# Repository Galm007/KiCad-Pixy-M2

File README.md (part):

# Pixy-M2 — Micromouse Controller PCB

A controller for a micromouse robot. **On this branch (`devkit-daughterboard`)
the MCU is an ESP32-S3-DevKitC-1-N8R8 plugged into two SMD female headers.**
The board carries two **DRV8231A** motor drivers with current regulation, a
**2S LiPo** power path with fusing, switching and UVLO, a **3.3 V buck**, and
connectors for four **VL53L0X** time-of-flight wall sensors, a **BNO085** IMU
and two **Pololu N20** gearmotors with encoders.

Designed in **KiCad 10**. 4-layer, 66 × 100 mm, fully placed and routed.

| | |
|---|---|
| **MCU** | ESP32-S3-DevKitC-1-**N8R8** (v1.1; 8 MB flash, 8 MB octal PSRAM) on two 1×22 SMD female headers. USB-UART and native-USB ports, BOOT/RESET on the devkit |
| **Power in** | 2S LiPo (7.4 V nominal, 8.4 V full) via XT30. The devkit's USB powers the 3.3 V rail on the bench |
| **Logic rail** | 3.3 V, AP63203 2 A synchronous buck |
| **Motor drive** | 2 × TI DRV8231A H-bridge, 0.828 A nominal hardware current limit, per-motor current sense into the ADC |
| **Sensors** | 4 × VL53L0X ToF (I²C), BNO085 9-DoF IMU (SPI), 2 × 12 CPR quadrature encoders |
| **Protection** | 1500 A-breaking battery fuse, 600 W TVS on the motor rail, hardware UVLO (the devkit carries its own USB protection) |
| **PCB** | 66 × 100 mm, 4 layers, 1.6 mm, 79 footprints, 233 vias, 2.20 m of track |
| **Status** | Schematic complete, ERC 0/0. Layout routed, DRC 0 violations / 0 unconnected / 0 parity. **Not yet fabricated.** |

---

## Contents

- [Board renders](#board-renders)
- [Schematic](#schematic)
- [System architecture](#system-architecture)
- [Design decisions](#design-decisions)
- [Pin and connector reference](#pin-and-connector-reference)
- [PCB layout](#pcb-layout)
- [Parts list](#parts-list)
- [Repository layout](#repository-layout)
- [Working with the project](#working-with-the-project)
- [Bring-up notes for firmware](#bring-up-notes-for-firmware)
- [Status and open items](#status-and-open-items)
- [License](#license)

---

## Board renders

The top of each image is the **front** of the robot: the four ToF sensor
mounts face the maze walls ahead. The devkit stands on its sockets along the
right edge with its antenna over the rear edge. The devkit has no 3D model, so
the renders show Espressif's WROOM-1 model at the module's real height
(11.6 mm) with nothing under it: it floats above the sockets where the
devkit's own PCB would be.

<table>
  <tr>
    <td align="center"><br><b>Top</b></td>
    <td align="center"><br><b>Bottom</b> (mirrored)</td>
  </tr>
</table>

The silkscreen prints where each off-board part attaches:

- **Top:** the four ToF mounts with their aim arrows and the connector each
  cable plugs into, the BNO085 breakout outline (8.6 mm left of the rotation
  centre, beside the devkit), and an arrow between the socket rows toward the
  end that takes the devkit's USB ports.
- **Bottom:** the two Pololu HP 6V gearmotors, with the gearbox face on the
  board edge and the shaft on the wheel axle. `ENC CONN SIDE` marks the face
  their encoder boards stand proud of, which must point outboard. Between the
  motors is the 2S battery's outline, with an arrow at the end its leads
  leave from and a dashed line for the lead's route round the left edge to
  BT1.

---

## Schematic

Single flat A3 sheet: [`Pixy-M2.kicad_sch`](Pixy-M2.kicad_sch).

---

## System architecture

```mermaid
flowchart LR
    BAT["2S LiPo<br/>XT30 (BT1)"] --> F1["F1<br/>5 A fuse<br/>1500 A break"]
    F1 --> Q1["Q1 P-FET<br/>switched by SW3"]
    Q1 -- VBAT --> DRV["U4 / U5<br/>DRV8231A ×2"]
    Q1 -- VBAT --> D6["D6 TVS<br/>SMBJ9.0A"]
    Q1 -- VBAT --> D2["D2<br/>Schottky"]
    D2 -- VSYS --> BUCK["U3 AP63203<br/>3.3 V buck"]
    BUCK -- BUCK_3V3 --> ISO["U8 / Q2<br/>USB-priority isolation"]
    ISO -- ESP_3V3 --> MCU["U1 DevKitC-1<br/>3V3 pins"]
    ISO -- ESP_3V3 --> PERIPH["ToF ×4, IMU,<br/>encoders"]
    USB["devkit USB ports"] --> LDO["devkit LDO"]
    LDO -- 3V3 --> MCU
    DRV --> MOT["J8 / J9<br/>N20 motors + encoders"]
    MCU <-->|I²C| TOF["J4–J7<br/>VL53L0X ×4"]
    MCU <-->|SPI| IMU["J10<br/>BNO085"]
```

### Power path

```
 BT1+ ── F1 ── VBAT_FUSED ── Q1 (S→D) ── VBAT ──┬── D2 ── VSYS ── U3 buck ── BUCK_3V3 ── U8/Q2 ── ESP_3V3 ── devkit 3V3 pins
                   │            │                ├── U4/U5 motor drivers
                  R14           G                ├── R7/R8 UVLO divider
                   └────────────┤                ├── R10/R11 battery sense
                           SW3 (gate only)       └── D6 TVS to GND
```

- **`VBAT`** is the switched, fused motor rail. Motor current does **not** pass
  through D2. D2 feeds only the buck input.
- **`VSYS`** is the pack through D2, **~8.1 V** on a full pack.
- **`BUCK_3V3`** is the buck's regulated output, including L1, C7/C11 and
  its unchanged feedback path. U8 and Q2 feed the separate **`ESP_3V3`** rail.
- **`ESP_3V3`** feeds the devkit's 3V3 pins, sensors, encoders and LEDs.
  U6 supplies the drivers' separate **`MOTOR_VREF`**, nominally 1.242 V.
- **USB has priority.** U1's 5V pin is used only for voltage sensing through
  R28/R29. With USB present, U8 disables and Q2 opens, isolating the buck from
  the devkit LDO. Their opposing body diodes block either direction while off.
  USB therefore supplies the complete logic load; the 800 mA LDO rating alone
  does not establish a safe continuous load. Begin USB bring-up with RF off and
  measure rail voltage and LDO temperature at the intended load.
- **USB removal with the pack on is bridged by C30.** U8 needs ~40 µs to turn
  on once the devkit's LDO drops out; C30 (100 µF X5R) with C1/C15 holds
  ESP_3V3 meanwhile: ≈0.2 V sag at 0.25 A, ≈0.42 V at 0.5 A (conservative,
  without the devkit's own capacitance). Scope it before relying on it.
  USB-only operation leaves the motors inhibited through U6/U7. No on-board
  charging; charge the pack separately.

---

## Design decisions

The rules and rejected alternatives that must not regress are summarised in
[`CLAUDE.md`](CLAUDE.md). The measurements behind each change are under
[`layout/`](layout/), and the full history is in the git log. This section
covers the main choices.

### The MCU as a plug-in DevKitC-1 (this branch)

The ESP32-S3 is an off-the-shelf **ESP32-S3-DevKitC-1-N8R8** on two 1×22
female headers, not a soldered WROOM module. The devkit brings its USB ports,
its USB-UART bridge with auto-reset, its BOOT/RESET buttons and its CHIP_PU RC.
That takes the USB-C input, its ESD array and PPTC, the CC and shield parts,
the USB supply path into VSYS, the reset/boot network and the programming
header off this board, along with the routed USB pair and its impedance
question.

- **Placement.** The devkit is 25.4 × 62.7 mm and fits only along the right
  edge, antenna over the rear edge as before. The board outline is unchanged
  at 66 × 100 mm. The left corner stays the motor and power region; the IMU
  moves into the 25 mm column left beside the devkit, 8.6 mm off the rotation
  centre.
- **SMD sockets.** The devkit's area lies over the underside battery bay and
  motor B; through-hole socket tails would stand into both.
- **Power.** The board's AP63203 feeds the devkit's 3V3 pins, so the verified
  buck block stays. The alternative, a 5 V buck into the devkit's 5V pin,
  would have OR-ed cleanly with USB through the devkit's diodes, but it meant
  redesigning the buck and running everything from an 800 mA LDO.
- **Pins.** The N8R8's octal PSRAM takes GPIO35–37 and the v1.1 board's RGB LED
  takes GPIO38. Encoder B's OUT B moved from GPIO38 to GPIO18, the last spare.
  No GPIO is left spare.
- **Costs.** About 10 mm more height, the devkit's mass, and friction-fit
  headers in a robot that hits walls: retain the devkit before running.

An earlier version put the motors, drivers and IMU on a daughterboard instead,
through two 22-pin headers. That one carried motor return current through the
headers; this one keeps all the power and motor copper on the main board.

### Motor driver: TI DRV8231A

The driver has to survive what the TVS lets through, not just the 8.4 V pack.
D6 clamps `VBAT` at up to **15.4 V**, and that ruled out the usual micromouse
parts:

| Part | VM abs max | Verdict |
|---|---:|---|
| DRV8833 | 11.8 V | below the clamp: rejected |
| TB6612FNG | 15.0 V | below the clamp: rejected |
| DRV8874 / DRV8876 | 40 V | good, but no stock KiCad symbol |
| **DRV8231A** | **35 V** | **fitted**, 2.3× the clamp |

The DRV8231A also:

- runs down to **4.5 V**, which covers the whole usable pack range;
- has **internal 100 kΩ pulldowns on IN1/IN2**, so both motors stay off while
  the ESP32's GPIOs float at reset;
- needs no nSLEEP or nFAULT pin, which saves GPIOs;
- has **integrated current regulation and an `IPROPI` sense output**.

### Current limit: 0.828 A nominal, with connector margin

```
ITRIP = VREF / (AIPROPI × RIPROPI) = 1.242 V / (1500 µA/A × 1 kΩ) = 0.828 A
```

U6's reference replaces the 3.3 V rail at the two driver VREF pins. R17/R18
are **1 kΩ 1 %, ≤100 ppm/°C**. The JST SH contacts and Pololu cable are rated
1 A; the previous 1.00 A nominal setting left no tolerance margin. With the
reference, temperature and resistor corners included, the trip comparator has
about 108 mV margin at 1 A using TI's minimum specified mirror gain. That gain
bound is specified at 1 A and VM ≥6.5 V, so it is not a guarantee on every PWM
peak. Check current ripple and stall heating on hardware.

IPROPI now reads **1.5 V/A** on GPIO2/GPIO10 (ADC1), about 1.242 V at the nominal
limit. Firmware must update its scaling and stop sustained stalls. Details and
calculation assumptions are in [the power integrity audit](layout/power-integrity/README.md).

### Battery fuse: one-time, 1500 A breaking

The chosen pack is a 2S 450 mAh 100C LiPo. Its estimated dead-short current is
**200–400 A**. The original 3 A PPTC could only break 40 A, so it was replaced
with a **Littelfuse 0885005.DR**: 5 A fast-acting, 1500 A breaking at
125 VDC. Normal load is below the old ~2.4 A allowance after lowering both motor
limits. Measure acceleration peaks before changing any fuse or current-limit value. Slow overload protection is now the job of the driver current limit and
firmware stall detection. F1 only opens on a real fault.

### Hardware undervoltage lockout

The buck's `EN` pin has a built-in comparator with switched hysteresis. A 1 %
divider (R7/R8) on `VBAT` sets it to:

| | Pack voltage | Per cell |
|---|---:|---:|
| Turn on | 6.90 V | 3.45 V |
| Turn off | 5.94 V | 2.97 V |

This controls the **buck only**. It cannot stop a USB-powered MCU from driving
motors. The added U6 comparator independently monitors VBAT through R24/R25,
with R26 hysteresis. U7 disconnects all four driver inputs below its threshold;
the drivers' internal pulldowns then command coast regardless of firmware.
U6's power-on reset and R27 keep the switches disabled during logic startup.

| Motor inhibit | Pack voltage | Per cell |
|---|---:|---:|
| Enable on rising battery | 6.75 V | 3.37 V |
| Coast on falling battery | 6.35 V | 3.17 V |

R24/R25/R26 (100 k / 23.2 k / 825 k) are **0.1 %, ≤25 ppm/°C** thin film. Over
−40 to +125 °C the DC envelopes are 6.01–6.74 V (coast) and 6.39–7.08 V
(enable), so a pack resting at 3.6 V/cell always enables the motors. The
inhibit is a hardware **backstop under firmware's own cutoff** (about 6.8 V
under load, latched so a rebounding pack cannot restart a stalled motor).
Below VM 6.5 V the DRV8231A still regulates current; TI just does not
specify its ±6 % mirror accuracy there. (The 2026-10-14 version cut off at
6.92 V and enabled at 7.39 V to stay inside that condition, which cost the
bottom third of the pack.) Filter delay and fast dips need scope checks.
USB does not reach REG_EN.

### Battery sense without a gate FET

`VBAT` → 470 kΩ / 220 kΩ → GPIO1 (ADC1_CH0), with a 100 nF reservoir cap.

- The divider draws 12 µA, well under the 58 µA of the UVLO divider, which
  cannot be gated. A gate FET would save almost nothing.
- A low-side gate would have been harmful: the sense node floats up into the
  GPIO clamp.
- A full-pack reading sits at 2.68 V. Even a badly overcharged 9.5 V pack reads
  3.03 V, still inside the ADC's range.
- Both dividers are downstream of Q1, so SW3 OFF removes their drain on the
  pack.

### Buck converter

- The **AP63203WU** is a fixed 3.3 V part, so it needs no feedback divider.
- **L1 is a Bourns SRP5030T-4R7M** (Isat 6 A, 53 mΩ). It replaced an 0805
  inductor that would have saturated at a few hundred mA.
- **C17 straddles the package under U3**, across IN and GND, which is the
  tightest input loop the pinout allows. C12 (22 µF 25 V 1206) is the bulk. It
  keeps ~11–13 µF at 8.4 V bias, which meets the datasheet's 10 µF effective
  input capacitance.
- **The switch node is 3.57 mm² of top copper with no vias.** TP4 hangs off it
  as a short stub.

### Input diode

D2 is an **onsemi MBRA340T3G** (40 V, 3 A, SMA). It carries only the buck's
input, ~0.43 A worst case, so an ideal-diode controller is not worth it. The
40 V rating covers the 15.4 V TVS clamp reaching `VSYS`. It also blocks the
devkit's USB from back-feeding `VBAT` through the buck.

### IMU on SPI, not I²C

The BNO085 could have shared the ToF I²C bus on throughput alone. It was put
on its own SPI bus for **latency**: an IMU interrupt that arrives mid-way
through a ToF read would wait up to ~150 µs, which is 15 % of a 1 kHz control
period. SCK, MOSI and MISO are on the ESP32-S3's native FSPI pins, so they go
through the IO MUX rather than the GPIO matrix. INT and RST are wired because
the BNO08x needs both for stable SPI. WAKE shares a pin with PS0 on the module.

### Four ToF sensors on one I²C bus

Every VL53L0X powers up at address `0x29`, and the address is volatile. Each
sensor therefore gets its own XSHUT line (GPIO4–7), so firmware can release the
sensors one at a time and re-address them. R15/R16 (2.2 kΩ) are the only bus
pull-ups, placed near the host, as the datasheet recommends. J4–J7 use the
GY-VL53L0XV2 module's own header order, so the cable is a straight 1:1 loom.

### USB

On the devkit. Its native-USB port (USB-Serial-JTAG) gives flashing, console
and debugging; its USB-UART port gives esptool auto-reset. Each port reaches
the devkit's 5 V rail through a 1N5819. This board senses that rail at U1.21
for USB priority; it does not draw supply power from it.

### Strapping pins

GPIO45 and GPIO46 carry explicit no-connect flags. Driving GPIO45 high at reset
sets the flash rail to 1.8 V and the board will not boot. GPIO46 high with
GPIO0 low is an invalid boot combination. GPIO0 is the devkit's BOOT button.
GPIO3 is the safe one of the four, and drives the green status LED
active-high, so its reset state stays low.

### Capacitor ratings

Every capacitor's voltage rating is in its Value field, so it shows on the
schematic. One is worth pointing out:

- **C19/C21** (motor bulk) are **22 µF 25 V** because of the 15.4 V TVS clamp.

---

## Pin and connector reference

### GPIO allocation

Every GPIO the devkit leaves usable is allocated; none is spare.

| Function | GPIO |
|---|---|
| Devkit USB D− / D+ (not wired here) | 19 / 20 |
| Devkit BOOT button (not wired here) | 0 |
| Battery sense (ADC1_CH0) | 1 |
| Status LED (green, active high) | 3 |
| ToF XSHUT 1–4 (J4–J7) | 4, 5, 6, 7 |
| I²C SDA / SCL (ToF bus) | 8 / 9 |
| Motor A IN1 / IN2 | 39 / 40 |
| Motor B IN1 / IN2 | 41 / 42 |
| Motor A / B current sense (IPROPI, ADC1) | 2 / 10 |
| Encoder A: OUT A / OUT B | 47 / 48 |
| Encoder B: OUT A / OUT B | 21 / 18 |
| IMU SPI SCK / MOSI / MISO / CS | 12 / 11 / 13 / 14 |
| IMU INT / RST / WAKE (PS0) | 15 / 16 / 17 |
| Devkit USB-UART TX / RX (not wired here) | 43 / 44 |
| N8R8 octal PSRAM / v1.1 RGB LED (not wired here) | 35, 36, 37 / 38 |
| Strapping, deliberately no-connect | 45, 46 |

### Connectors

All the signal connectors are **JST SH 1.0 mm side-entry**.

**J4–J7: VL53L0X ToF sensors** (`SM06B-SRSS-TB`, GY-VL53L0XV2 header order)

| Pin | 1 | 2 | 3 | 4 | 5 | 6 |
|---|---|---|---|---|---|---|
| Signal | **VCC 3.3 V** | GND | SCL | SDA | INT (NC) | XSHUT |

> ⚠️ Pin 1 is **VCC**, not GND. A cable built "the usual way round" puts
> 3.3 V on the sensor's ground.

| Connector | Position | XSHUT |
|---|---|---|
| J4 | Front left (FL) | GPIO4 |
| J5 | Front right (FR) | GPIO5 |
| J6 | Look-ahead left, 45° | GPIO6 |
| J7 | Look-ahead right, 45° | GPIO7 |

**J8 / J9: motor + encoder** (`SM06B-SRSS-TB`, Pololu 12 CPR encoder order)

| Pin | 1 | 2 | 3 | 4 | 5 | 6 | MP |
|---|---|---|---|---|---|---|---|
| Signal | GND | OUT B | OUT A | VCC 3.3 V | M2 | M1 | GND |
| Pololu wire | green | white | yellow | blue | black | red | — |

J8 is motor A (left) and J9 is motor B (right). Use Pololu's straight SH–SH
encoder cable (#4765–#4769). R19–R22 pull the encoder outputs up to 3.3 V.

**J10: BNO085 IMU** (`SM09B-SRSS-TB`)

| Pin | 1 | 2 | 3 | 4 | 5 | 6 | 7 | 8 | 9 |
|---|---|---|---|---|---|---|---|---|---|
| Signal | VIN 3.3 V | GND | SCK | MOSI | MISO | CS | INT | RST | WAKE / PS0 |

> ⚠️ Jumper **PS1 high** on the module. Stock BNO08x breakouts ship in I²C mode
> and will not answer on SPI until it is changed.

**U1: the DevKitC-1** (two 1×22 2.54 mm SMD female headers)

The devkit plugs in with its **USB ports toward the front** of the robot: the
silkscreen arrow between the rows points that way, and `3V3`/`GND` mark pins
1/44 at the antenna end. Turned round, it puts the 3.3 V rail on GND pins.
Its USB-UART port is the way back in if firmware ever disables the native USB.

**Other**

| Ref | Part | Purpose |
|---|---|---|
| BT1 | XT30U-M | 2S LiPo input |
| SW3 | C&K JS102011SAQN slide | Battery ON/OFF (gate control only) |
| D4 / D5 | Red / green LED | Power (always on) / status (GPIO3), rear-left corner |
| TP1–TP4 | Test pads | VBAT, 3V3, GND, SW node (TP4 is under the devkit's USB end; TP2/TP3 sit between J5 and J7) |
| TP9 | Test pad | Probe GND |
| TP10, TP11 | Test pads | MOTOR_OK (rear left), MOTOR_VREF (beside the motor corner). BUCK_3V3 is probed at L1 or C26, in front of the devkit |

---

## PCB layout

### Stackup

4 layers, 1.6 mm, designed for **JLC04161H-7628** (~0.2 mm L1–L2 prepreg).

| Layer | Use |
|---|---|
| **L1** F.Cu | Components, buck switch node, motor-driver power loops, ground pour around the motor region |
| **L2** In1.Cu | **Solid, unbroken GND plane.** No signals, no splits. |
| **L3** In2.Cu | `ESP_3V3` pour plus a separate `VBAT` island under the motor region |
| **L4** B.Cu | Secondary routing plus a GND pour stitched to L2 |

The ground plane is never split. Noise is controlled by **placement**
instead. The motor drivers, the bulk capacitors, D6 and the battery entry
share the left-hand region. The devkit, ADC nodes and I²C sit away from it.

<p align="center">
  <br>
  <em>Top copper (F.Cu). The 0.8 mm motor trunks, the 1.0 mm battery path and the motor-region ground pour are on the left.</em>
</p>

### Layout highlights

- **Every trace is straight 0/45/90° runs with 45° turns.** The grid router's
  staircases, which rendered as curves, are rebuilt as clear straight legs by
  the last copper stage ([`layout/octilinear/`](layout/octilinear/README.md)).
  Only hand-placed copper keeps its own geometry: the buck block, the driver
  pin escapes and their bypass loops, ten short stubs in all off 45°.
- **Motor outputs** are 0.8 mm trunks. The only narrower copper is inside
  each driver's own pin field, and a custom DRC rule enforces that. Each pair
  runs together to its connector: the loop areas are **25.9 mm²** (A) and
  **24.3 mm²** (B).
- **Driver thermal pads** each have two filled-and-capped in-pad vias
  (IPC-4761 type VII) plus four more nearby. Only two fit a 0.9 × 1.6 mm pad
  under the hole-to-hole rule.
- **VM bypass caps** sit 1.33 mm from each driver's VM pin, across VM and GND.
  The loop closes in top copper with no plane hop.
- **Antenna keep-out**: the devkit's antenna overhangs the rear edge ~10 mm
  above the board, with an all-layer copper keep-out under its edge defined as
  a board rule area.
- **The devkit stands on SMD sockets.** Its courtyard is the two socket
  bodies; low parts (C1/C2, the I²C and encoder pull-ups) sit between the rows
  under it.
- **Rules are encoded, not just followed.** Netclasses and
  [`Pixy-M2.kicad_dru`](Pixy-M2.kicad_dru) enforce:
  - motor trunk width;
  - power and battery path widths;
  - a 0.2 mm signal floor;
  - clearance floors keeping `REG_EN`, `VBAT_SENSE` and the IPROPI lines away
    from motor and switching copper.

  Each rule was tested by breaking a copy of the board and checking that DRC
  fired.

The board was routed by a purpose-written A* grid router
([`tools/autoroute/`](tools/autoroute/)) and then reworked in stages, each
driven by a design review. Every stage is scripted and reproducible. The review
findings and the evidence for each fix (DRC reports, measurements,
before/after images) are under [`layout/`](layout/).

---

## Parts list

Parts for **one robot**, taken from **[`BOM.md`](BOM.md)**. BOM.md also has
each part's status, the cable wiring, the mechanical parts and the tools. The
shopping list below has one line per part to buy.

### Shopping list

Quantities are exact, with no spares except the crimp contacts. Where BOM.md
lets one part fill several positions, the list merges them: one 0.1 µF 50 V
part covers all twelve 0.1 µF positions. R24–R26 must be 0.1 % and ≤25 ppm/°C; other
resistors may be 1 %. R17/R18 and R28/R29 must also be ≤100 ppm/°C.

| Qty | Part | For |
|---:|---|---|
| 1 | Espressif **ESP32-S3-DevKitC-1-N8R8** (v1.1) | U1, plugged in. Not an `R8V`/`R16V` variant (1.8 V GPIO47/48) |
| 2 | 1×22 2.54 mm vertical **SMD** female header, Harwin M20-786 land pattern | U1's sockets. Part number open: see BOM.md |
| 2 | TI **DRV8231ADSGR** | U4, U5 |
| 1 | Diodes Inc **AP63203WU-7** | U3. Fixed 3.3 V, not the AP63200 |
| 1 | TI **TLV3012BIDBVR** | U6; B version required |
| 1 | TI **SN74LV4066APWR** | U7 |
| 1 | TI **LM66100DCKR** | U8 |
| 1 | AOS **AO3401A** | Q2 |
| 1 | onsemi **MMBT3904LT1G** | Q3 |
| 1 | AOS **AO4407A** | Q1. Not the IRF7404 the symbol names |
| 1 | onsemi **MBRA340T3G** | D2 |
| 1 | Vishay **SMBJ9.0A-E3/52** | D6 |
| 1 | Red LED, high-efficiency, 0805 | D4. Must be visibly lit at ~150 µA |
| 1 | Green LED, 0805 | D5 |
| 1 | Bourns **SRP5030T-4R7M** | L1 |
| 1 | Littelfuse **0885005.DR** | F1 |
| 1 | C&K **JS102011SAQN** | SW3 |
| 1 | AMASS **XT30U-M** | BT1 |
| 6 | JST **SM06B-SRSS-TB(LF)(SN)** | J4–J9 |
| 1 | JST **SM09B-SRSS-TB(LF)(SN)** | J10 |
| 12 | 0.1 µF 50 V X7R, 0603 | C2, C6, C13, C14, C16–C18, C20, C22–C24, C27 |
| 1 | 2.2 nF 16 V X7R, 0603 | C25 |
| 1 | 4.7 nF 16 V X7R, 0603 | C28 |
| 1 | 1 µF 16 V X7R, 0603 | C26 |
| 1 | Murata **GRM31CR60J107ME39L**, 100 µF 6.3 V X5R, 1206 | C30 |
| 2 | 10 µF 16 V X5R/X7R, 0805 | C1, C15 |
| 2 | 22 µF 16 V X5R/X7R, 0805 | C7, C11 |
| 3 | 22 µF 25 V X5R/X7R, 1206 | C12, C19, C21 |
| 7 | 10 kΩ 1 %, 0805 | R12, R19–R23, R28 |
| 3 | 2.2 kΩ 1 %, 0805 | R13, R15, R16 |
| 2 | 1 kΩ 1 %, ≤100 ppm/°C, 0805 | R17/R18, RC0805FR-071KL |
| 1 | 82 kΩ 1 %, 0805 | R29 |
| 1 | Yageo **RT0805BRD07100KL**, 100 kΩ 0.1 % 25 ppm, 0805 | R24 |
| 1 | Yageo **RT0805BRD0723K2L**, 23.2 kΩ 0.1 % 25 ppm, 0805 | R25 |
| 1 | Yageo **RT0805BRD07825KL**, 825 kΩ 0.1 % 25 ppm, 0805 | R26 |
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
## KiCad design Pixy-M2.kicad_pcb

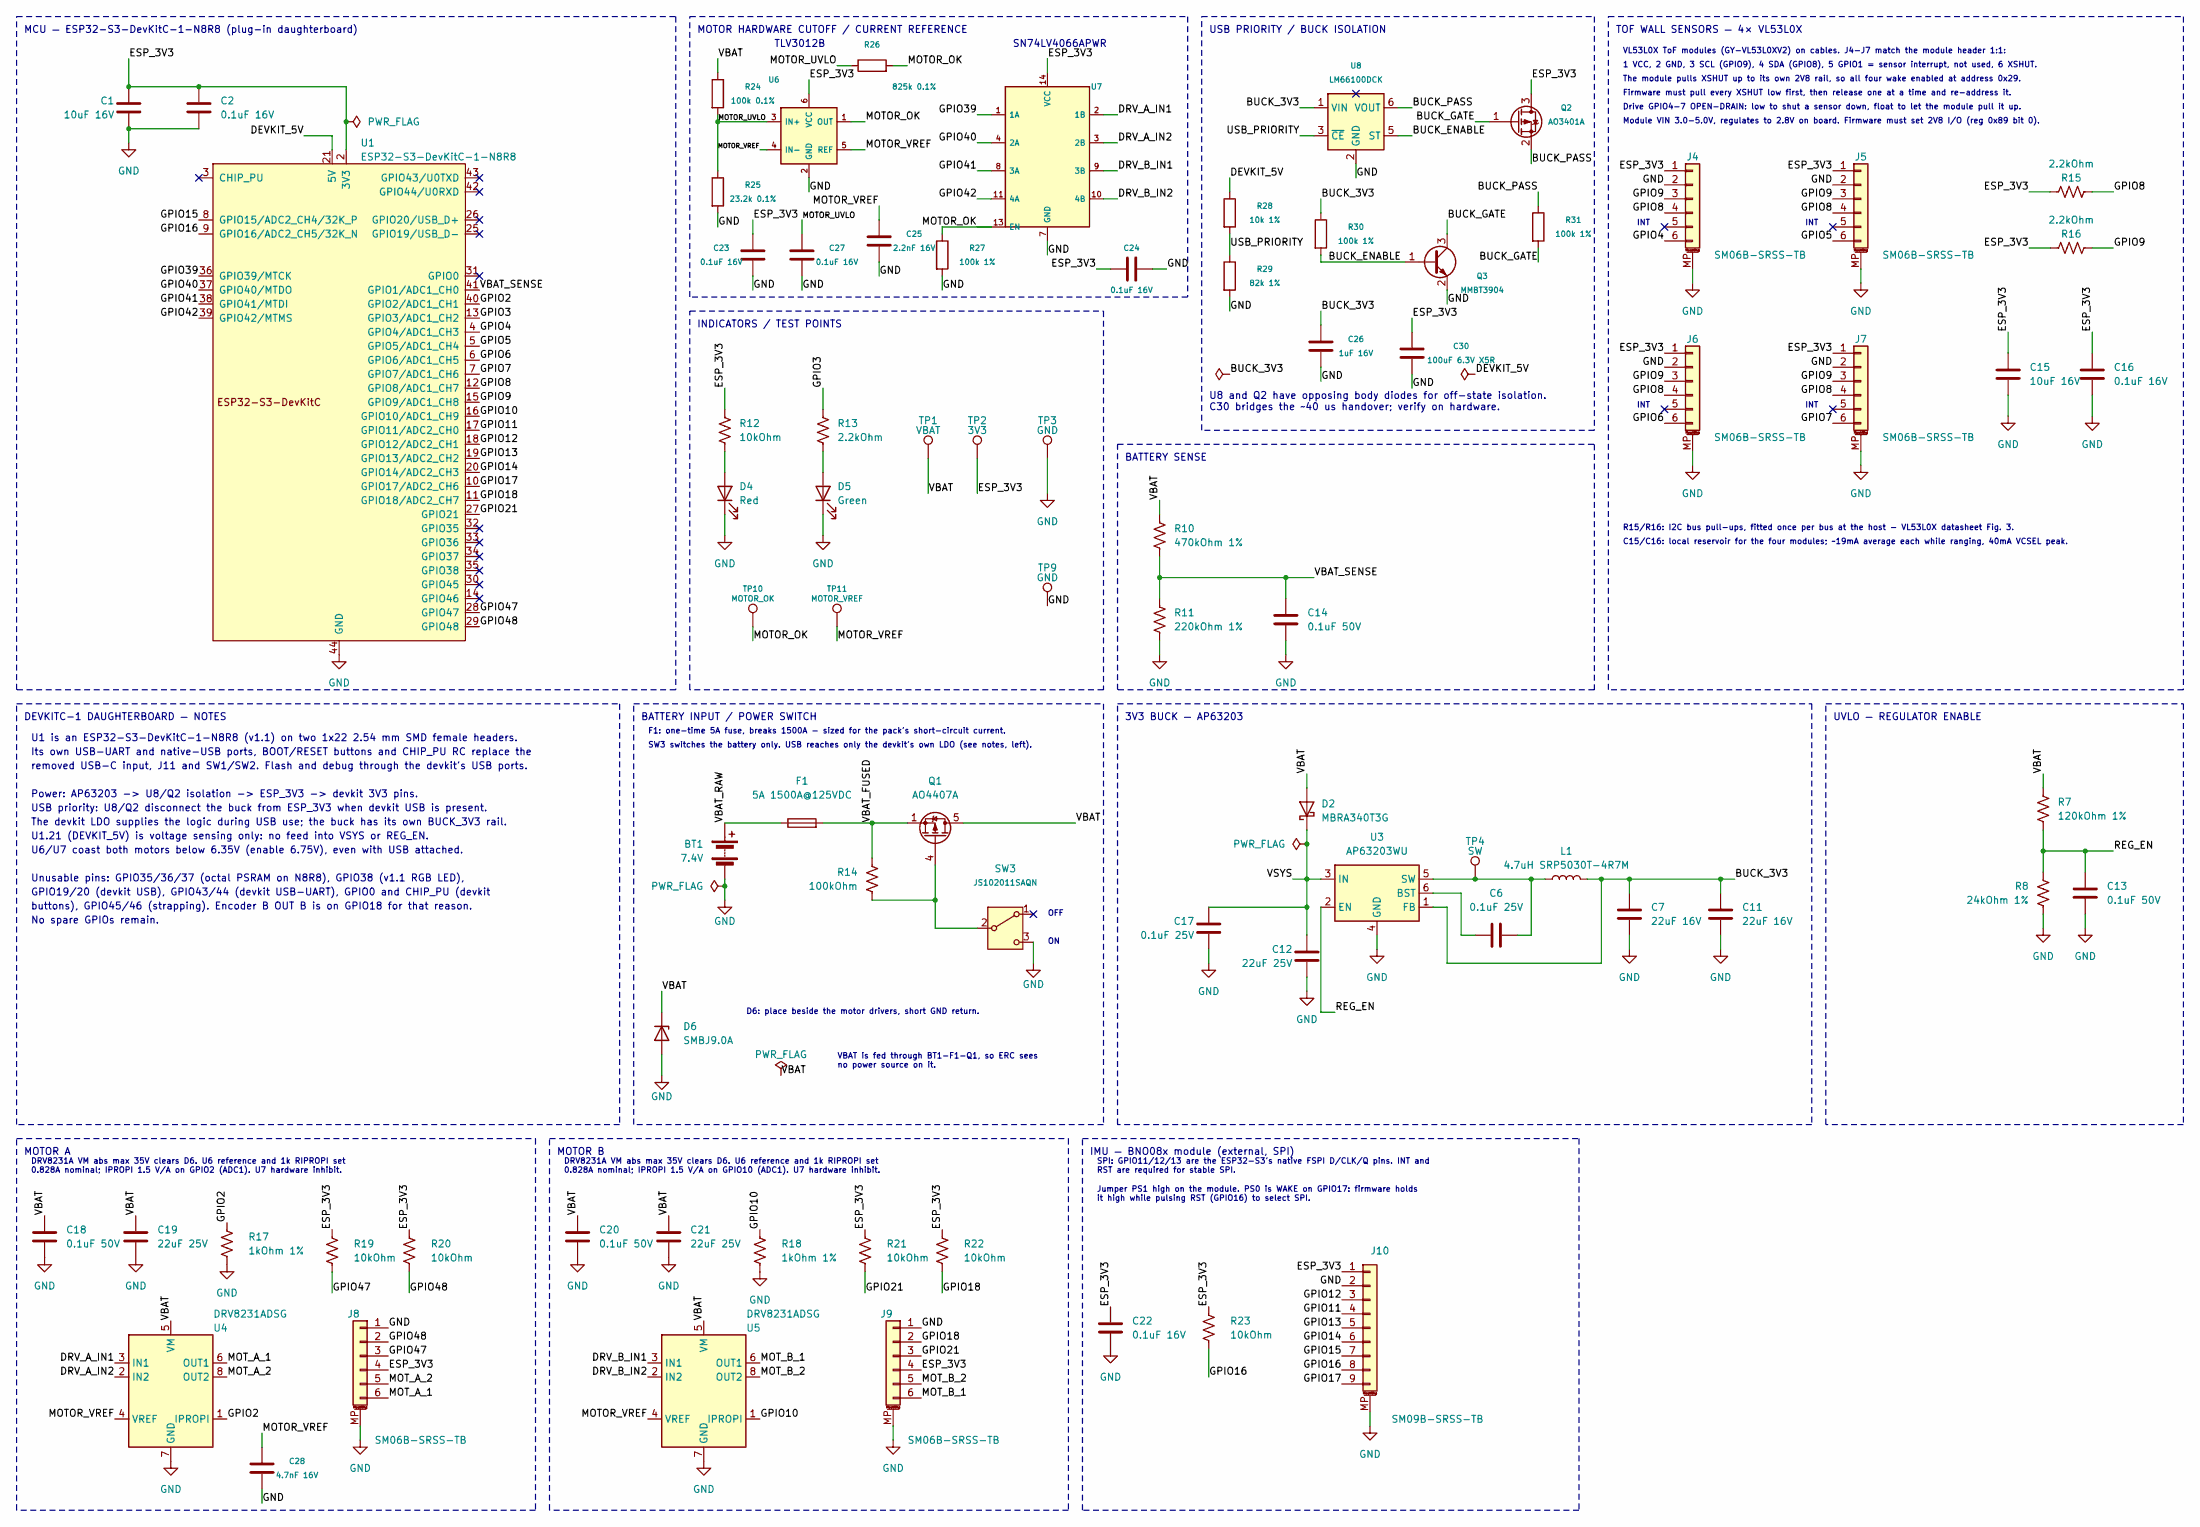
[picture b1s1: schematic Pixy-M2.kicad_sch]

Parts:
BT1: 7.4V; AMASS_XT30U-M_1x02_P5.0mm_Vertical
C1, C15: 10uF 16V; C_0805_2012Metric
C2, C16, C22, C23, C24, C27: 0.1uF 16V; C_0603_1608Metric
C6, C17: 0.1uF 25V; C_0603_1608Metric
C7, C11: 22uF 16V; C_0805_2012Metric
C12, C19, C21: 22uF 25V; C_1206_3216Metric
C13, C14, C18, C20: 0.1uF 50V; C_0603_1608Metric
C25: 2.2nF 16V; C_0603_1608Metric
C26: 1uF 16V; C_0603_1608Metric
C28: 4.7nF 16V; C_0603_1608Metric
C30: 100uF 6.3V X5R; C_1206_3216Metric; MPN GRM31CR60J107ME39L
D2: MBRA340T3G; D_SMA; MPN MBRA340T3G
D4: Red; LED_0805_2012Metric
D5: Green; LED_0805_2012Metric
D6: SMBJ9.0A; D_SMB; MPN SMBJ9.0A-E3/52
F1: 5A 1500A@125VDC; Fuse_Littelfuse-NANO2-885; MPN 0885005.DR
J4, J5, J6, J7, J8, J9: SM06B-SRSS-TB; JST_SH_SM06B-SRSS-TB_1x06-1MP_P1.00mm_Horizontal; MPN SM06B-SRSS-TB(LF)(SN)
J10: SM09B-SRSS-TB; JST_SH_SM09B-SRSS-TB_1x09-1MP_P1.00mm_Horizontal
L1: 4.7uH SRP5030T-4R7M; L_Bourns_SRP5030T; MPN SRP5030T-4R7M
Q1: AO4407A; SOIC-8_3.9x4.9mm_P1.27mm; MPN AO4407A
Q2: AO3401A; SOT-23; MPN AO3401A
Q3: MMBT3904; SOT-23; MPN MMBT3904LT1G
R7: 120kOhm 1%; R_0805_2012Metric
R8: 24kOhm 1%; R_0805_2012Metric
R10: 470kOhm 1%; R_0805_2012Metric
R11: 220kOhm 1%; R_0805_2012Metric
R12, R19, R20, R21, R22, R23: 10kOhm; R_0805_2012Metric
R13, R15, R16: 2.2kOhm; R_0805_2012Metric
R14: 100kOhm; R_0805_2012Metric
R17, R18: 1kOhm 1%; R_0805_2012Metric; MPN RC0805FR-071KL
R24: 100k 0.1%; R_0805_2012Metric; MPN RT0805BRD07100KL
R25: 23.2k 0.1%; R_0805_2012Metric; MPN RT0805BRD0723K2L
R26: 825k 0.1%; R_0805_2012Metric; MPN RT0805BRD07825KL
R27, R30, R31: 100k 1%; R_0805_2012Metric
R28: 10k 1%; R_0805_2012Metric
R29: 82k 1%; R_0805_2012Metric
SW3: JS102011SAQN; SW_SPDT_CK_JS102011SAQN; MPN JS102011SAQN
TP1: VBAT; TestPoint_Pad_D1.5mm
TP2: 3V3; TestPoint_Pad_D1.5mm
TP3, TP9: GND; TestPoint_Pad_D1.5mm
TP4: SW; TestPoint_Pad_D1.5mm
TP10: MOTOR_OK; TestPoint_Pad_D1.5mm
TP11: MOTOR_VREF; TestPoint_Pad_D1.5mm
U1: ESP32-S3-DevKitC-1-N8R8; ESP32-S3-DevKitC-1_SMD_Sockets; MPN ESP32-S3-DevKitC-1-N8R8
U3: AP63203WU; TSOT-23-6
U4, U5: DRV8231ADSG; Texas_DSG0008A_WSON-8-1EP_2x2mm_P0.5mm_EP0.9x1.6mm; MPN DRV8231ADSGR
U6: TLV3012B; SOT-23-6; MPN TLV3012BIDBVR
U7: SN74LV4066APW; TSSOP-14_4.4x5mm_P0.65mm; MPN SN74LV4066APWR
U8: LM66100DCK; SOT-363_SC-70-6; MPN LM66100DCKR

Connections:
/BUCK_3V3: C7.1, C11.1, C26.1, L1.2, R30.1, U3.1 (FB), U8.1 (VIN)
/BUCK_ENABLE: Q3.1 (B), R30.2, U8.5 (ST)
/BUCK_GATE: Q2.1 (G), Q3.3 (C), R31.2
/BUCK_PASS: Q2.2 (S), R31.1, U8.6 (VOUT)
/DEVKIT_5V: R28.1, U1.21 (5V)
/DRV_A_IN1: U4.3 (IN1), U7.2 (1B)
/DRV_A_IN2: U4.2 (IN2), U7.3 (2B)
/DRV_B_IN1: U5.3 (IN1), U7.9 (3B)
/DRV_B_IN2: U5.2 (IN2), U7.10 (4B)
/ESP_3V3: C1.1, C2.1, C15.1, C16.1, C22.1, C23.1, C24.1, C30.1, J4.1, J5.1, J6.1, J7.1, J8.4, J9.4, J10.1, Q2.3 (D), R12.1, R15.1, R16.1, R19.1, R20.1, R21.1, R22.1, R23.1, TP2.1, U1.1 (3V3), U1.2 (3V3), U6.6 (VCC), U7.14 (VCC)
/GPIO2: R17.1, U1.40 (GPIO2/ADC1_CH1), U4.1 (IPROPI)
/GPIO3: R13.1, U1.13 (GPIO3/ADC1_CH2)
/GPIO4: J4.6, U1.4 (GPIO4/ADC1_CH3)
/GPIO5: J5.6, U1.5 (GPIO5/ADC1_CH4)
/GPIO6: J6.6, U1.6 (GPIO6/ADC1_CH5)
/GPIO7: J7.6, U1.7 (GPIO7/ADC1_CH6)
/GPIO8: J4.4, J5.4, J6.4, J7.4, R15.2, U1.12 (GPIO8/ADC1_CH7)
/GPIO9: J4.3, J5.3, J6.3, J7.3, R16.2, U1.15 (GPIO9/ADC1_CH8)
/GPIO10: R18.1, U1.16 (GPIO10/ADC1_CH9), U5.1 (IPROPI)
/GPIO11: J10.4, U1.17 (GPIO11/ADC2_CH0)
/GPIO12: J10.3, U1.18 (GPIO12/ADC2_CH1)
/GPIO13: J10.5, U1.19 (GPIO13/ADC2_CH2)
/GPIO14: J10.6, U1.20 (GPIO14/ADC2_CH3)
/GPIO15: J10.7, U1.8 (GPIO15/ADC2_CH4/32K_P)
/GPIO16: J10.8, R23.2, U1.9 (GPIO16/ADC2_CH5/32K_N)
/GPIO17: J10.9, U1.10 (GPIO17/ADC2_CH6)
/GPIO18: J9.2, R22.2, U1.11 (GPIO18/ADC2_CH7)
/GPIO21: J9.3, R21.2, U1.27 (GPIO21)
/GPIO39: U1.36 (GPIO39/MTCK), U7.1 (1A)
/GPIO40: U1.37 (GPIO40/MTDO), U7.4 (2A)
/GPIO41: U1.38 (GPIO41/MTDI), U7.8 (3A)
/GPIO42: U1.39 (GPIO42/MTMS), U7.11 (4A)
/GPIO47: J8.3, R19.2, U1.28 (GPIO47)
/GPIO48: J8.2, R20.2, U1.29 (GPIO48)
/MOTOR_OK: R26.2, R27.1, TP10.1, U6.1 (OUT), U7.5, U7.6, U7.12, U7.13 (EN)
/MOTOR_UVLO: C27.1, R24.2, R25.1, R26.1, U6.3 (IN+)
/MOTOR_VREF: C25.1, C28.1, TP11.1, U4.4 (VREF), U5.4 (VREF), U6.4 (IN-), U6.5 (REF)
/MOT_A_1: J8.6, U4.6 (OUT1)
/MOT_A_2: J8.5, U4.8 (OUT2)
/MOT_B_1: J9.6, U5.6 (OUT1)
/MOT_B_2: J9.5, U5.8 (OUT2)
/REG_EN: C13.1, R7.2, R8.1, U3.2 (EN)
/USB_PRIORITY: R28.2, R29.1, U8.3 (~CE)
/VBAT: C18.1, C19.1, C20.1, C21.1, D2.2 (A), D6.1 (K), Q1.5 (D), Q1.6 (D), Q1.7 (D), Q1.8 (D), R7.1, R10.1, R24.1, TP1.1, U4.5 (VM), U5.5 (VM)
/VBAT_FUSED: F1.2, Q1.1 (S), Q1.2 (S), Q1.3 (S), R14.1
/VBAT_RAW: BT1.1 (+), F1.1
/VBAT_SENSE: C14.1, R10.2, R11.1, U1.41 (GPIO1/ADC1_CH0)
/VSYS: C12.1, C17.1, D2.1 (K), U3.3 (IN)
GND: BT1.2 (-), C1.2, C2.2, C7.2, C11.2, C12.2, C13.2, C14.2, C15.2, C16.2, C17.2, C18.2, C19.2, C20.2, C21.2, C22.2, C23.2, C24.2, C25.2, C26.2, C27.2, C28.2, C30.2, D4.1 (K), D5.1 (K), D6.2 (A), J4.2, J4.MP (MountPin), J5.2, J5.MP (MountPin), J6.2, J6.MP (MountPin), J7.2, J7.MP (MountPin), J8.1, J8.MP (MountPin), J9.1, J9.MP (MountPin), J10.2, J10.MP (MountPin), Q3.2 (E), R8.2, R11.2, R17.2, R18.2, R25.2, R27.2, R29.2, SW3.3 (C), TP3.1, TP9.1, U1.22 (GND), U1.23 (GND), U1.24 (GND), U1.44 (GND), U3.4 (GND), U4.7 (GND), U4.9 (GND), U5.7 (GND), U5.9 (GND), U6.2 (GND), U7.7 (GND), U8.2 (GND)
unnamed: D4.2 (A), R12.2
unnamed: D5.2 (A), R13.2
unnamed: Q1.4 (G), R14.2, SW3.2 (B)
unnamed: C6.1, U3.6 (BST)
unnamed: C6.2, L1.1, TP4.1, U3.5 (SW)

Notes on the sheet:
OFF
F1: one-time 5A fuse, breaks 1500A - sized for the pack's short-circuit current.
SW3 switches the battery only. USB reaches only the devkit's own LDO (see notes, left).
D6: place beside the motor drivers, short GND return.
INT
VL53L0X ToF modules (GY-VL53L0XV2) on cables. J4-J7 match the module header 1:1:
1 VCC, 2 GND, 3 SCL (GPIO9), 4 SDA (GPIO8), 5 GPIO1 = sensor interrupt, not used, 6 XSHUT.
The module pulls XSHUT up to its own 2V8 rail, so all four wake enabled at address 0x29.
Firmware must pull every XSHUT low first, then release one at a time and re-address it.
Drive GPIO4-7 OPEN-DRAIN: low to shut a sensor down, float to let the module pull it up.
Module VIN 3.0-5.0V, regulates to 2.8V on board. Firmware must set 2V8 I/O (reg 0x89 bit 0).
R15/R16: I2C bus pull-ups, fitted once per bus at the host - VL53L0X datasheet Fig. 3.
C15/C16: local reservoir for the four modules; ~19mA average each while ranging, 40mA VCSEL peak.
MOTOR A
DRV8231A VM abs max 35V clears D6. U6 reference and 1k RIPROPI set 0.828A nominal; IPROPI 1.5 V/A on GPIO2 (ADC1). U7 hardware inhibit.
MOTOR B
DRV8231A VM abs max 35V clears D6. U6 reference and 1k RIPROPI set 0.828A nominal; IPROPI 1.5 V/A on GPIO10 (ADC1). U7 hardware inhibit.
VBAT is fed through BT1-F1-Q1, so ERC sees no power source on it.
IMU — BNO08x module (external, SPI)
SPI: GPIO11/12/13 are the ESP32-S3's native FSPI D/CLK/Q pins. INT and RST are required for stable SPI.
Jumper PS1 high on the module. PS0 is WAKE on GPIO17: firmware holds it high while pulsing RST (GPIO16) to select SPI.
MCU — ESP32-S3-DevKitC-1-N8R8 (plug-in daughterboard)
INDICATORS / TEST POINTS
BATTERY SENSE
TOF WALL SENSORS — 4× VL53L0X
DEVKITC-1 DAUGHTERBOARD — NOTES
BATTERY INPUT / POWER SWITCH
3V3 BUCK — AP63203
UVLO — REGULATOR ENABLE
U1 is an ESP32-S3-DevKitC-1-N8R8 (v1.1) on two 1x22 2.54 mm SMD female headers.
Its own USB-UART and native-USB ports, BOOT/RESET buttons and CHIP_PU RC replace the
removed USB-C input, J11 and SW1/SW2. Flash and debug through the devkit's USB ports.
Power: AP63203 -> U8/Q2 isolation -> ESP_3V3 -> devkit 3V3 pins.
USB priority: U8/Q2 disconnect the buck from ESP_3V3 when devkit USB is present.
The devkit LDO supplies the logic during USB use; the buck has its own BUCK_3V3 rail.
U1.21 (DEVKIT_5V) is voltage sensing only: no feed into VSYS or REG_EN.
U6/U7 coast both motors below 6.35V (enable 6.75V), even with USB attached.
Unusable pins: GPIO35/36/37 (octal PSRAM on N8R8), GPIO38 (v1.1 RGB LED),
GPIO19/20 (devkit USB), GPIO43/44 (devkit USB-UART), GPIO0 and CHIP_PU (devkit
buttons), GPIO45/46 (strapping). Encoder B OUT B is on GPIO18 for that reason.

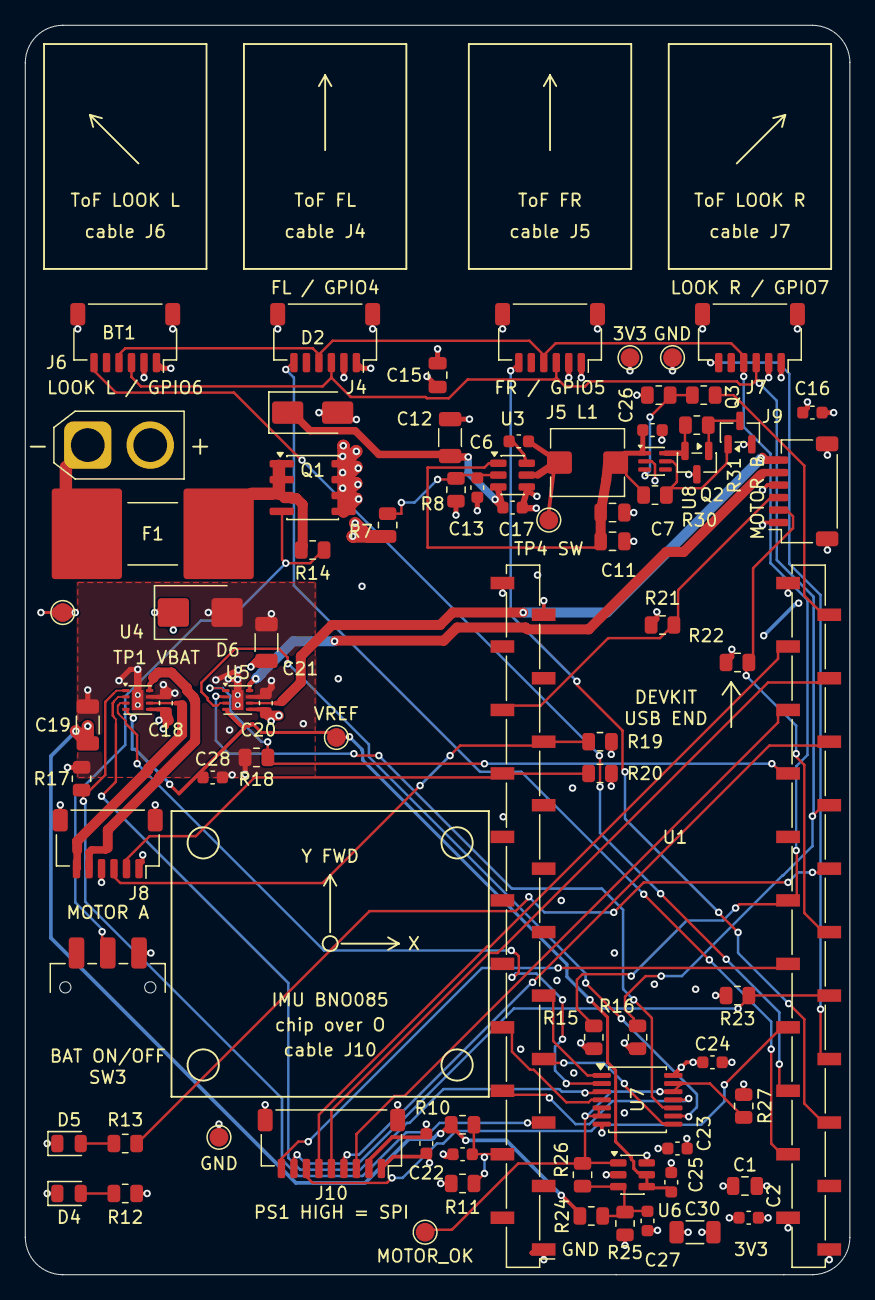
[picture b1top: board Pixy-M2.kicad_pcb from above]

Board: 4 copper layers, 66.0 x 100.0 mm, 79 parts (0 on the bottom side), 54 nets.

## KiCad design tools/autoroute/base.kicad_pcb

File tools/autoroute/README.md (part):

# autoroute — the grid router used to wire Pixy-M2 on 2026-09-21

Not a general tool. It was written for this board and hard-codes its net names,
widths and the In2.Cu VBAT island.

    python3 wire.py      # reads base.kicad_pcb, writes ../../Pixy-M2.kicad_pcb
    python3 rework.py    # reads base-routed.kicad_pcb, writes ../../Pixy-M2.kicad_pcb
    python3 check.py     # per-net length / width / via report on the routed board
    python3 loop.py -v   # motor output pair loop areas (add paths to compare boards)

A full `rework.py` run takes a few minutes: the via-out-of-pad pass recomputes a
per-net distance field for each via it moves. Run it in the background rather than
waiting on it, and **do not watch it with `pgrep -f "python3 rework.py"`** — the
pattern matches the watching shell's own command line, so the loop never exits.

## wire.py — the original routing pass

`wire.py` expects an *unrouted* copy of the board as `base.kicad_pcb` in its working
directory, and rewrites the project file from scratch every run — it never edits
existing tracks. Re-running it discards all hand edits made since, so copy the board
aside first.

How it works: pads and holes are rasterised onto a 0.05 mm grid; per net a Euclidean
distance transform gives the legal region for that net's width (0.26 mm clearance
target against a 0.2 mm rule); A* over F.Cu + B.Cu with a via cost routes each net,
growing a connected group at a time. Plane nets get one stitching via per SMD pad
instead of being routed. A final pass widens power tracks wherever clearance allows.

Two tracks in the committed board were hand-corrected afterwards and are not
reproduced by a re-run: one ESP_3V3 segment at U4 narrowed 0.4 → 0.2 mm, and a short
segment added so MOT_B_2 lands on J9 pad 6's annulus rather than its rounded corner.

## rework.py — the motor-region second pass (review issues 1–3)

`rework.py` reads **`base-routed.kicad_pcb`**, a snapshot of `wire.py`'s output, and
writes the reworked board. Like `wire.py` it never edits the file it reads, so it is
re-runnable — but it also discards any hand edits made to `Pixy-M2.kicad_pcb` since,
and it emits the board with *unfilled* zones. Always follow it with:

    kicad-cli pcb drc --schematic-parity --refill-zones --save-board \
        --format json -o /tmp/drc.json ../../Pixy-M2.kicad_pcb

What it does, in order — the order matters:

1. moves C18, C20, C21 and four silkscreen reference fields (footprint moves must
   come before any track edit: they re-split the file and drop pending block edits);
2. rips the four motor nets, `/GPIO6`, and the VBAT/GND stubs in five boxes around
   the old capacitor and driver positions;
3. lays the hand-computed copper — driver pin escapes, the VM/GND runs across to each
   bypass cap, and the in-pad thermal vias — all of it clearance-checked by hand
   against the 0.5 mm pin pitch rather than searched;
4. routes the four motor trunks at 0.8 mm with A*.  `MOT_B_1` goes first; its
   finished polyline is then sampled, each sample offset 1.15 mm toward the side
   `MOT_B_2` has to end up on, and `MOT_B_2` is routed through those points so the
   two run as a pair (review issue 4).  An unreachable waypoint is skipped, not
   fatal.  `U4` is not paired — measured, no gain, see CLAUDE.md;
5. *then* searches for the plane stitching vias, so they cannot land on a trunk;
6. lays the buck block (`buck_block`, review issue 5) — same discipline: every
   track first, every via afterwards.  The first attempt did it the other way and
   dropped a ground stitching via straight into the corridor the switch node
   needed, shorting SW to GND under the package;
7. re-routes `/VSYS` (through a waypoint north of the buck, or A* threads the
   8.4 V input rail between L1 and the output capacitors), `/REG_EN` and
   `/GPIO6`, all of which were ripped to free space;
8. runs the historical centre-based relocation (`unstick_vias`) and its whole-net
   fallback. This stage alone misses drill-edge overlaps and paste-only pads;
   it is retained to reproduce the original routing, then corrected in step 10;
9. restores the verified local GPIO48 route with `encoder48_cleanup` (2026-09-22
   audit P3). The generic via relocation had stretched this encoder net to
   72.36 mm around TP5 and J11; the replacement is 26.03 mm, keeps the J8/R20/U1
   connections, and puts all four via holes at least 0.45 mm clear of SMD mask
   openings. This runs after the generic reroute so regeneration preserves it;
10. applies `finish_issue6.py`: 35 local via moves and their layer connections,
    with per-via fill/cap on the four intentional driver thermal vias;
11. lays the USB pair (`usb_pair.py`, review issue 7).  It rips the four USB
    nets and CC1/CC2, turns U2 to rot 90 so its flow-through pins face J1 and
    U1, hand-places the 0.25 / 0.15 mm pair J1 → U2 → U1 on F.Cu with no vias,
    takes U2's GND and VBUS out under the body, then A*-routes CC1/CC2 with the
    pair inflated 0.15 mm so they cross it on B.Cu and keep their vias clear.
    It runs last so that every stage before it replays unchanged; the U2 move
    therefore goes through `Pcb.sync()` (below) rather than the up-front MOVES;
12. lays the copper the issue-8 rule set requires (`issue8.py`): widens the five
    nets the router left at 0.15 mm to 0.2 mm outside the DRV8231A pin fields,
    re-routes the USB supply (`Net-(F2-Pad1)`, `/VBUS`) at 0.6 mm with the D3 tap
    pinned to its old corridor, and the R14 tap on `/VBAT_FUSED` at 0.8 mm;
13. moves J8/J9 to JST SH in the Pololu encoder pin order (`pololu_conn.py`,
    2026-09-23).  It swaps the two PH footprints for SH clones of J4, rips the
    motor trunks back to the driver escapes, drops other-net copper under the
    new pad rows, prunes what that leaves dangling *within 2 mm of the new
    pads only*, then re-routes: 0.6 mm fan-in stubs and paired 0.8 mm trunks on
    M1/M2, 0.2 mm reconnections for the cut signals, plane stitches for GND,
    VCC and the MP pads, and U4's VREF feed (its B.Cu run to the old
    through-hole J8 pin was the only 3V3 path under the In2 VBAT island).
    It also sets R17/R18 to 2.2 kΩ.  `! no stitch via for GND near …` for
    J8.1, J8's west MP and J9.1 is **expected**: those pads are then tied to
    the nearest stitched pad or GND via;
14. replaces F1 with a Littelfuse 885 fuse (`f1_fuse.py`, 2026-09-23): builds
    the footprint from the stock library file, moves BT1 0.4 mm north so its
    courtyard fits, drops the stubs left on the old 2920 pads, and re-routes
    `/VBAT_RAW` and `/VBAT_FUSED` at 1.0 mm;
15. points U1 at the project footprint `Pixy-M2:ESP32-S3-WROOM-1_AntennaOverhang`
    (`Pcb.set_fpid`), matching the schematic, so the placed copy matches its
    library (see `layout/drc-clean/`);
16. prints the assembly marks on the silkscreen (`assembly_marks.py`,
    2026-09-23): the four ToF mount outlines with aim arrows and connector
    names, the Adafruit BNO085 outline with its holes, chip centre and X/Y
    axes on F.SilkS, and both Pololu N20 bodies on their wheel axles on
    B.SilkS.  It nudges the C20 and R15 reference fields clear of the IMU
    outline.  Standalone, it adds the marks to an existing board once;
17. moves the battery bay between the axles (`battery_bay.py`, 2026-09-24):
    the underside battery rule area goes to board x 0.5-66, y 57.5-74.5 (the
    62 x 17 mm pack plus its lead exit), both motor reservations turn their
    4 mm encoder allowance outboard, and User.1 / User.2 are redrawn to match,
    with the pack's lead route to BT1.  On B.SilkS it prints the pack
    outline, its lead arrow and the route as a dashed line (the motor names
    and `ENC CONN SIDE` come from `assembly_marks.py`).  Every edit asserts
    the placement-era geometry it replaces.  Standalone, it converts an
    existing board once, moving the motor names on a board marked before
    2026-09-24, and checks every drilled pad against the new envelopes and
    bands;
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
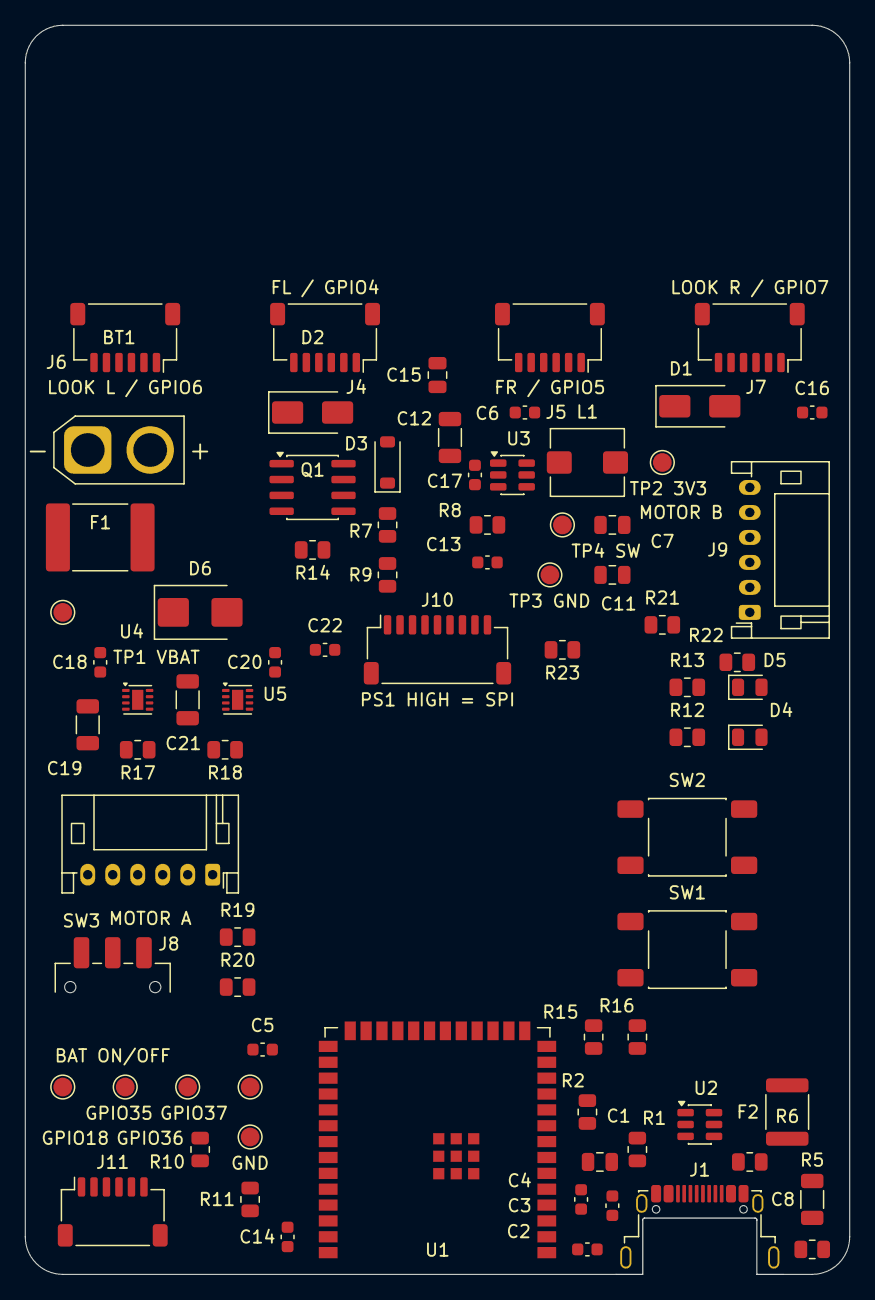
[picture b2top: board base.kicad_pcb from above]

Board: 4 copper layers, 66.0 x 100.0 mm, 78 parts (0 on the bottom side), 59 nets, no tracks yet.

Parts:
BT1: 7.4V; AMASS_XT30U-M_1x02_P5.0mm_Vertical
C1, C15: 10uF 16V; C_0805_2012Metric
C2, C4, C5, C16, C22: 0.1uF 16V; C_0603_1608Metric
C3: 1uF 16V; C_0603_1608Metric
C6, C17: 0.1uF 25V; C_0603_1608Metric
C7, C11: 22uF 16V; C_0805_2012Metric
C8: 4.7nF 1kV; C_1206_3216Metric
C12, C19, C21: 22uF 25V; C_1206_3216Metric
C13, C14, C18, C20: 0.1uF 50V; C_0603_1608Metric
D1, D2: MBRA340T3G; D_SMA
D3: BAT54W; D_SOD-123
D4: Red; LED_0805_2012Metric
D5: Green; LED_0805_2012Metric
D6: SMBJ9.0A; D_SMB
F1: 3A 15V; Fuse_2920_7451Metric
F2: 500mA 15V; Fuse_1812_4532Metric
J1: USB_C_Receptacle_USB2.0_14P; USB_C_Receptacle_Amphenol_12401948E412A
J4, J5, J6, J7, J11: SM06B-SRSS-TB; JST_SH_SM06B-SRSS-TB_1x06-1MP_P1.00mm_Horizontal
J8, J9: S6B-PH-K; JST_PH_S6B-PH-K_1x06_P2.00mm_Horizontal
J10: SM09B-SRSS-TB; JST_SH_SM09B-SRSS-TB_1x09-1MP_P1.00mm_Horizontal
L1: 4.7uH SRP5030T-4R7M; L_Bourns_SRP5030T
Q1: AO4407A; SOIC-8_3.9x4.9mm_P1.27mm
R1, R6: 5.1kOhm; R_0805_2012Metric
R2, R12, R19, R20, R21, R22, R23: 10kOhm; R_0805_2012Metric
R5: 1MOhm; R_0805_2012Metric
R7: 120kOhm 1%; R_0805_2012Metric
R8: 24kOhm 1%; R_0805_2012Metric
R9: 39kOhm 1%; R_0805_2012Metric
R10: 470kOhm 1%; R_0805_2012Metric
R11: 220kOhm 1%; R_0805_2012Metric
R13, R15, R16: 2.2kOhm; R_0805_2012Metric
R14: 100kOhm; R_0805_2012Metric
R17, R18: 1.5kOhm 1%; R_0805_2012Metric
SW1, SW2: SW_Push; SW_Push_1P1T_NO_E-Switch_TL3301NxxxxxG
SW3: JS102011SAQN; SW_SPDT_CK_JS102011SAQN
TP1: VBAT; TestPoint_Pad_D1.5mm
TP2: 3V3; TestPoint_Pad_D1.5mm
TP3, TP9: GND; TestPoint_Pad_D1.5mm
TP4: SW; TestPoint_Pad_D1.5mm
TP5: GPIO18; TestPoint_Pad_D1.5mm
TP6: GPIO35; TestPoint_Pad_D1.5mm
TP7: GPIO36; TestPoint_Pad_D1.5mm
TP8: GPIO37; TestPoint_Pad_D1.5mm
U1: ESP32-S3-WROOM-1-N16; ESP32-S3-WROOM-1
U2: USBLC6-2SC6; SOT-23-6
U3: AP63203WU; TSOT-23-6
U4, U5: DRV8231ADSG; Texas_DSG0008A_WSON-8-1EP_2x2mm_P0.5mm_EP0.9x1.6mm

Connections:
/CHIP_PU: C3.1, C4.2, J11.6, R2.2, SW1.1, U1.3
/ESP_3V3: C1.1, C2.1, C7.1, C11.1, C15.1, C16.1, C22.1, J4.1, J5.1, J6.1, J7.1, J8.5, J9.5, J10.1, J11.1, L1.2, R2.1, R12.1, R15.1, R16.1, R19.1, R20.1, R21.1, R22.1, R23.1, TP2.1, U1.2, U3.1, U4.4, U5.4
/GPIO0: C5.2, J11.5, SW2.1, U1.27
/GPIO2: R17.1, U1.38, U4.1
/GPIO3: R13.1, U1.15
/GPIO4: J4.6, U1.4
/GPIO5: J5.6, U1.5
/GPIO6: J6.6, U1.6
/GPIO7: J7.6, U1.7
/GPIO8: J4.4, J5.4, J6.4, J7.4, R15.2, U1.12
/GPIO9: J4.3, J5.3, J6.3, J7.3, R16.2, U1.17
/GPIO10: R18.1, U1.18, U5.1
/GPIO11: J10.4, U1.19
/GPIO12: J10.3, U1.20
/GPIO13: J10.5, U1.21
/GPIO14: J10.6, U1.22
/GPIO15: J10.7, U1.8
/GPIO16: J10.8, R23.2, U1.9
/GPIO17: J10.9, U1.10
/GPIO18: TP5.1, U1.11
/GPIO21: J9.3, R21.2, U1.23
/GPIO35: TP6.1, U1.28
/GPIO36: TP7.1, U1.29
/GPIO37: TP8.1, U1.30
/GPIO38: J9.4, R22.2, U1.31
/GPIO39: U1.32, U4.3
/GPIO40: U1.33, U4.2
/GPIO41: U1.34, U5.3
/GPIO42: U1.35, U5.2
/GPIO43: J11.3, U1.37
/GPIO44: J11.4, U1.36
/GPIO47: J8.3, R19.2, U1.24
/GPIO48: J8.4, R20.2, U1.25
/MOT_A_1: J8.1, U4.6
/MOT_A_2: J8.6, U4.8
/MOT_B_1: J9.1, U5.6
/MOT_B_2: J9.6, U5.8
/REG_EN: C13.1, R7.2, R8.1, R9.2, U3.2
/USB_D+: U1.14, U2.4
/USB_D-: U1.13, U2.6
/VBAT: C18.1, C19.1, C20.1, C21.1, D2.2, D6.1, Q1.5, Q1.6, Q1.7, Q1.8, R7.1, R10.1, TP1.1, U4.5, U5.5
/VBAT_FUSED: F1.2, Q1.1, Q1.2, Q1.3, R14.1
/VBAT_RAW: BT1.1, F1.1
/VBAT_SENSE: C14.1, R10.2, R11.1, U1.39
/VBUS: D1.2, D3.2, F2.2, U2.5
/VSYS: C12.1, C17.1, D1.1, D2.1, U3.3
GND: BT1.2, C1.2, C2.2, C3.2, C4.1, C5.1, C7.2, C8.2, C11.2, C12.2, C13.2, C14.2, C15.2, C16.2, C17.2, C18.2, C19.2, C20.2, C21.2, C22.2, D4.1, D5.1, D6.2, J1.A1, J1.A12, J1.B1, J1.B12, J4.2, J4.MP, J5.2, J5.MP, J6.2, J6.MP, J7.2, J7.MP, J8.2, J9.2, J10.2, J10.MP, J11.2, J11.MP, R1.2, R5.2, R6.2, R8.2, R11.2, R17.2, R18.2, SW1.2, SW2.2, SW3.3, TP3.1, TP9.1, U1.1, U1.40, U1.41, U2.2, U3.4, U4.7, U4.9, U5.7, U5.9
unnamed: D3.1, R9.1
unnamed: D4.2, R12.2
unnamed: D5.2, R13.2
unnamed: F2.1, J1.A4, J1.A9, J1.B4, J1.B9
unnamed: J1.A5, R6.1
unnamed: J1.B5, R1.1
unnamed: J1.A6, J1.B6, U2.3
unnamed: J1.A7, J1.B7, U2.1
unnamed: C8.1, J1.SH, R5.1
unnamed: Q1.4, R14.2, SW3.2
unnamed: C6.1, U3.6
unnamed: C6.2, L1.1, TP4.1, U3.5

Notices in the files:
README.md:
License:
The design files, scripts and documentation in this repository are released
under the [MIT License](LICENSE).
Third-party material keeps its own terms:
- `DS_vl53l0x.pdf` is STMicroelectronics' datasheet, included for reference.
- `Pixy-M2.pretty/ESP32-S3-WROOM-1_AntennaOverhang.kicad_mod` (unused on this
branch) is derived from Espressif's KiCad footprint library and remains under
that library's license. The DevKitC-1 footprint's 3D view borrows Espressif's
WROOM-1 model by reference.
